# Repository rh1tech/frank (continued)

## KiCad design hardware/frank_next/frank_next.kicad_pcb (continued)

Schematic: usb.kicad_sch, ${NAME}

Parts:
C71: 100nF; C_0603_1608Metric
C72, C73: 100uF; CP_Elec_6.3x6.0
C74, C75, C79, C81, C83: 100nF; C_0603_1608Metric; LCSC C14663
C76, C77, C78, C80, C82, C84, C86, C87, C88: 10uF; C_0603_1608Metric; LCSC C96446
C85: 1uF; C_0603_1608Metric; LCSC C29936
C89, C90: 12pF; C_0603_1608Metric; LCSC C38523
C91: 22pF; C_0603_1608Metric; LCSC C1653
J10, J11: USB4215-03-A; USB_C_Receptacle; LCSC C37616412
JP4: USB Debug; SolderJumper-2_P1.3mm_Open_RoundedPad1.0x1.5mm
JP5: PWR Debug; SolderJumper-2_P1.3mm_Open_RoundedPad1.0x1.5mm
L5: 330R 2A; L_0805_2012Metric; LCSC C76819
L6: 2.2uH; L_Cenker_CKCS3015; LCSC C167747
LD3: Green; LED_0603_1608Metric; LCSC C965804
R49: 10K; R_0603_1608Metric
R50, R51, R52, R53: 5.1K; R_0603_1608Metric; LCSC C23186
R54: 300K; R_0603_1608Metric; LCSC C23024
R55, R58, R62: 100K; R_0603_1608Metric; LCSC C25803
R56: 1M; R_0603_1608Metric; LCSC C22935; not fitted
R57, R60: 1K; R_0603_1608Metric; LCSC C21190
R59: 10K; R_0603_1608Metric; LCSC C2906982
R61: 4.7K; R_0603_1608Metric; LCSC C23162; not fitted
R63: 22K; R_0603_1608Metric; LCSC C31850
S7: SS12D00; Switch_Slide_SS12D00; Mouser Part Number 611-SK12D07VG3NS
S8: SK12D07VG3NS; Switch_Slide_SK12D07VG3NS_PWR; Mouser Part Number 611-SK12D07VG3NS; LCSC C431547
U12: TS3USB221RSER; UQFN-10
U13, U14: TPD4S012DRYR; Mouser Part Number 595-TPD4S012DRYR; LCSC C96506
U15: TPS2116DRL; SOT-583-8; LCSC C3235557
U16: AO3401A; SOT-23-3L_AOS; LCSC C15127
U17: TS3USB221RSER; UQFN-10; LCSC C130085
U18: SY8089AAAC; SOT-23-5; LCSC C78988
U19: CH334F; QFN-24-1EP_4x4mm_P0.5mm_EP2.7x2.7mm; LCSC C5187527
Y4: 12 MHz; Crystal_SMD_3225-4Pin_3.2x2.5mm; LCSC C9002

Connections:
+3V3: C71.1, C81.2, C86.1, C87.1, C91.1, JP4.1 (A), L6.1, R49.1, R57.2, R62.1, S7.2, U12.10 (VCC), U17.10 (VCC); also elsewhere on the board
/CH343P/UD+: U12.1 (1D+); also elsewhere on the board
/CH343P/UD-: U12.2 (1D-); also elsewhere on the board
/RP2350A/D+: U12.3 (2D+); also elsewhere on the board
/RP2350A/D-: U12.4 (2D-); also elsewhere on the board
/RP2350B/D+: U17.8 (D+); also elsewhere on the board
/RP2350B/D-: U17.7 (D-); also elsewhere on the board
/USB/+5V_BUCK: C80.1, C82.1, C83.1, L5.2, U18.1 (EN), U18.4 (IN)
/USB/D2+: J10.6 (DP1), J10.8 (DP2), U13.1 (D+), U17.1 (1D+)
/USB/D2-: J10.5 (DN2), J10.7 (DN1), U13.2 (D-_), U17.2 (1D-)
/USB/DH+: U17.3 (2D+), U19.15 (DPU+)
/USB/DH-: U17.4 (2D-), U19.14 (DMU-)
/USB/DS1+: U19.12 (DP1+); also elsewhere on the board
/USB/DS1-: U19.11 (DM1-); also elsewhere on the board
/USB/DS2+: U19.10 (DP2+); also elsewhere on the board
/USB/DS2-: U19.9 (DM2-); also elsewhere on the board
/USB/DS3+: U19.8 (DP3+); also elsewhere on the board
/USB/DS3-: U19.7 (DM3-); also elsewhere on the board
/USB/OVCUR: U19.1 (~OVCUR); also elsewhere on the board
/USB/PWREN: U19.24 (~PWREN); also elsewhere on the board
/USB/S: JP4.2 (B), R59.2, S7.3, U17.9 (S)
/USB/ST: R56.2, U15.8 (ST)
/USB/USBC_D+: J11.6 (DP1), J11.8 (DP2), U12.8 (D+), U14.1 (D+)
/USB/USBC_D-: J11.5 (DN2), J11.7 (DN1), U12.7 (D-), U14.2 (D-_)
/USB/VBUS_IN: C78.1, C79.2, R58.2, U15.2 (VOUT), U15.7 (VOUT), U16.2 (S)
/USB/VBUS_IN1: C74.2, C76.2, J11.2 (VBUS), J11.11 (VBUS), R54.2, U14.6 (VBUS), U15.3 (VIN1), U15.5 (MODE)
/USB/VBUS_IN2: C75.2, C77.2, J10.2 (VBUS), J10.11 (VBUS), U13.6 (VBUS), U15.6 (VIN2)
/USB/VDD33: C84.2, C85.2, U19.20 (VDD33_{LDO})
/USB/XTAL_N: C89.1, U19.3 (XO), Y4.3
/USB/XTAL_P: C90.1, U19.4 (XI), Y4.1
/USB_SEL: R49.2, U12.9 (S); also elsewhere on the board
GND: C71.2, C72.2, C73.2, C74.1, C75.1, C76.1, C77.1, C78.2, C80.2, C81.1, C82.2, C83.2, C84.1, C85.1, C86.2, C87.2, C88.1, C89.2, C90.2, J10.1 (GND), J10.12 (GND), J10.13 (SHIELD), J11.1 (GND), J11.12 (GND), J11.13 (SHIELD), JP5.1 (A), LD3.1 (K), R50.1, R51.1, R52.1, R53.1, R55.1, R59.1, R61.2, R63.2, S8.2, U12.5 (GND), U12.6 (~OE), U13.4 (GND), U14.4 (GND), U15.1 (GND), U17.5 (GND), U17.6 (~OE), U18.2 (GND), U19.25 (GND), Y4.2, Y4.4; also elsewhere on the board
unnamed: J10.4 (CC1), R50.2
unnamed: J10.10 (CC2), R51.2
unnamed: J11.4 (CC1), R52.2
unnamed: J11.10 (CC2), R53.2
unnamed: JP5.2 (B), R60.2, S8.3
unnamed: LD3.2 (A), R57.1
unnamed: R54.1, R55.2, R56.1, U15.4 (PR1)
unnamed: C79.1, R58.1, R60.1, U16.1 (G)
unnamed: C91.2, R62.2, R63.1, U18.5 (FB)
unnamed: L6.2, U18.3 (LX)
unnamed: R61.1, U19.18 (PSELF)
VBUS: C72.1, C73.1, C88.2, L5.1, U16.3 (D), U19.19 (V5); also elsewhere on the board

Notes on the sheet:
USB-A shared VBUS bulk: C102 + C103 = 200 uF USB 2.0 7.2.4.1: >= 120 uF per hub, may be shared Kyocera AVX APZ0606101M016R 100 uF 16 V aluminium polymer, ESR 30 mOhm

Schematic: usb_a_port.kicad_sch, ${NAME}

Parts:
C95: 100nF; C_0603_1608Metric; LCSC C14663
C96: 10uF; C_0603_1608Metric; LCSC C96446
J12: 676430910; USB_A_Short; LCSC C2798029
R65: 100K; R_0603_1608Metric; LCSC C25803
U21: TPD4S012DRYR; Mouser Part Number 595-TPD4S012DRYR; LCSC C96506
U22: CH217K; SOT-23-6; LCSC C7462749

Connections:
/USB/DS1+: J12.3 (D+), U21.1 (D+); also elsewhere on the board
/USB/DS1-: J12.2 (D-), U21.2 (D-_); also elsewhere on the board
/USB/OVCUR: U22.3 (FLAG#); also elsewhere on the board
/USB/PWREN: U22.4 (EN#); also elsewhere on the board
/USB/USB A Port 1/VBUS_P: C95.1, J12.1 (VBUS), U21.6 (VBUS), U22.1 (VOUT)
GND: C95.2, C96.1, J12.4 (GND), J12.5 (Shield), R65.1, U21.4 (GND), U22.2 (GND); also elsewhere on the board
unnamed: R65.2, U22.5 (ISET)
VBUS: C96.2, U22.6 (VIN); also elsewhere on the board

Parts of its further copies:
C97, C99: 100nF; C_0603_1608Metric; LCSC C14663
C98, C101: 10uF; C_0603_1608Metric; LCSC C96446
J13, J14: 676430910; USB_A_Short; LCSC C2798029
R66, R70: 100K; R_0603_1608Metric; LCSC C25803
U23, U25: TPD4S012DRYR; Mouser Part Number 595-TPD4S012DRYR; LCSC C96506
U24, U27: CH217K; SOT-23-6; LCSC C7462749

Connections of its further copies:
/USB/DS2+: J13.3 (D+), U23.1 (D+); also elsewhere on the board
/USB/DS2-: J13.2 (D-), U23.2 (D-_); also elsewhere on the board
/USB/DS3+: J14.3 (D+), U25.1 (D+); also elsewhere on the board
/USB/DS3-: J14.2 (D-), U25.2 (D-_); also elsewhere on the board
/USB/OVCUR: U24.3 (FLAG#), U27.3 (FLAG#); also elsewhere on the board
/USB/PWREN: U24.4 (EN#), U27.4 (EN#); also elsewhere on the board
/USB/USB A Port 2/VBUS_P: C97.1, J13.1 (VBUS), U23.6 (VBUS), U24.1 (VOUT)
/USB/USB A Port 3/VBUS_P: C99.1, J14.1 (VBUS), U25.6 (VBUS), U27.1 (VOUT)
GND: C97.2, C98.1, C99.2, C101.1, J13.4 (GND), J13.5 (Shield), J14.4 (GND), J14.5 (Shield), R66.1, R70.1, U23.4 (GND), U24.2 (GND), U25.4 (GND), U27.2 (GND); also elsewhere on the board
unnamed: R66.2, U24.5 (ISET)
unnamed: R70.2, U27.5 (ISET)
VBUS: C98.2, C101.2, U24.6 (VIN), U27.6 (VIN); also elsewhere on the board

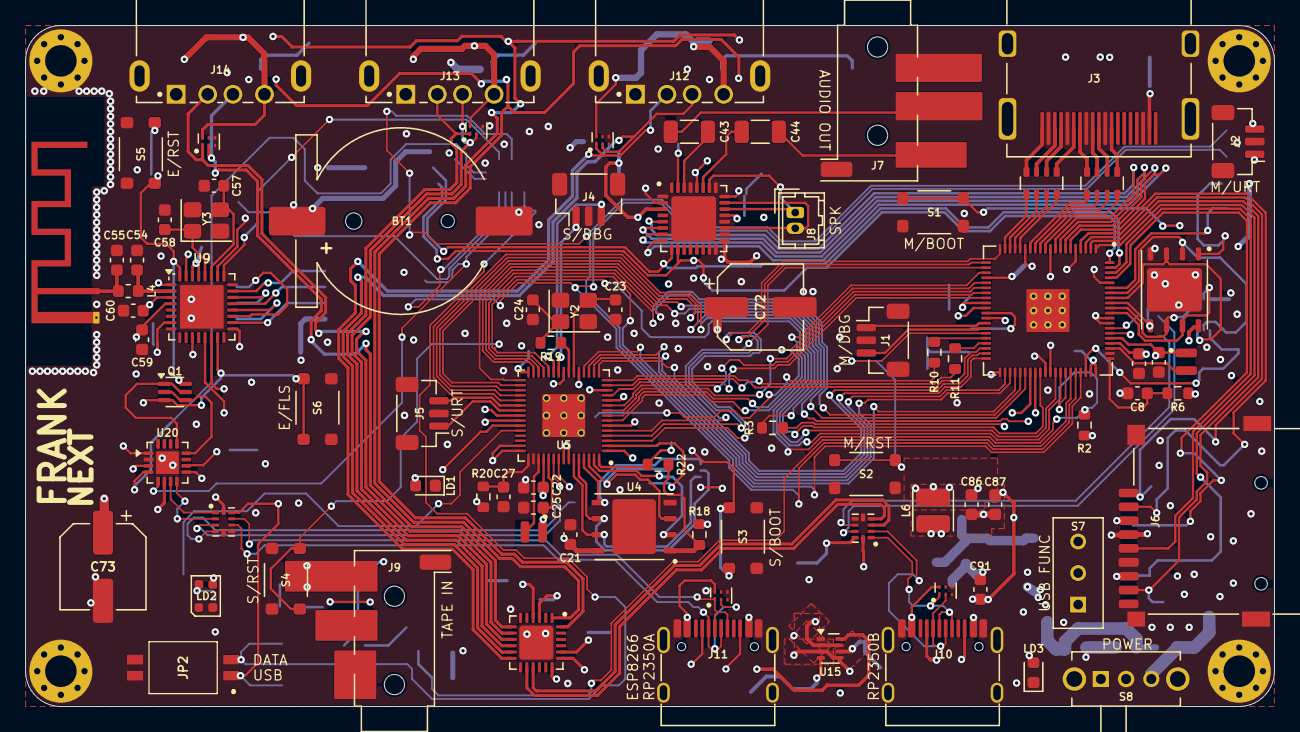
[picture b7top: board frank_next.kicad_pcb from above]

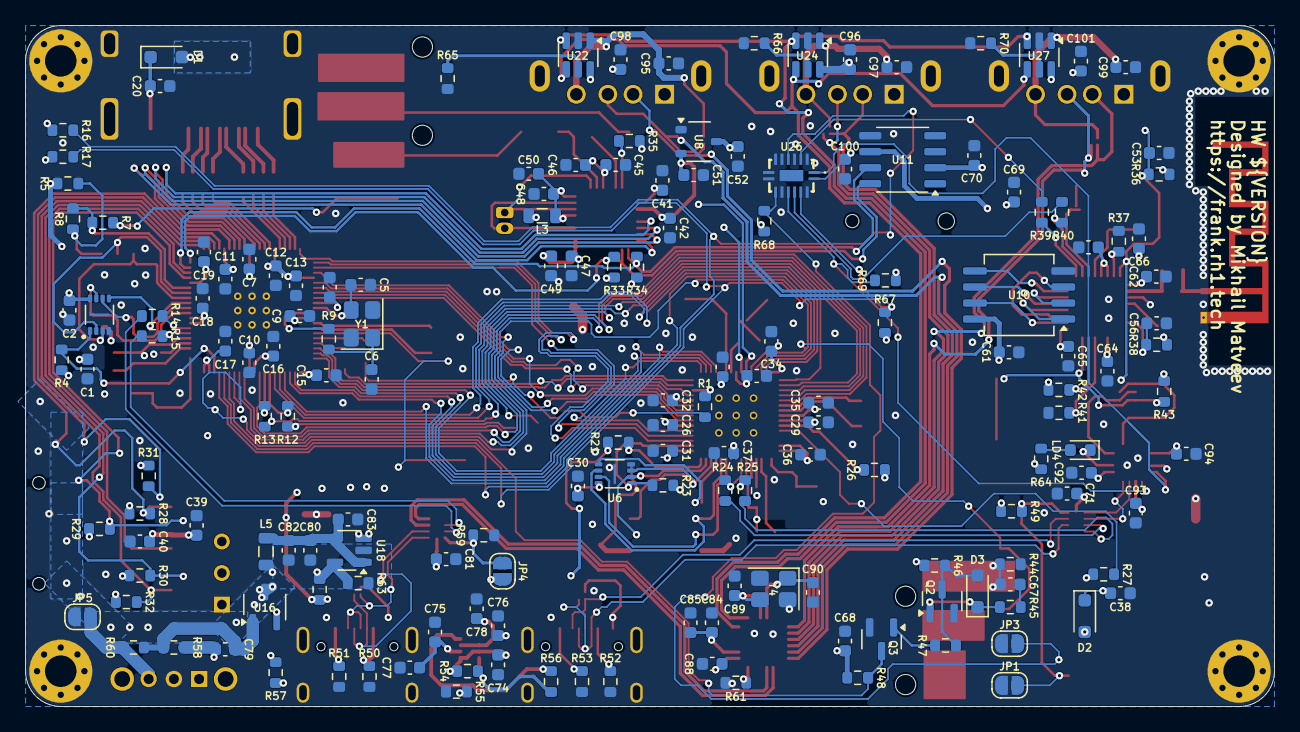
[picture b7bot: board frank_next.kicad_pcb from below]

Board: 4 copper layers, 99.0 x 54.0 mm, 253 parts (165 on the bottom side), 203 nets.

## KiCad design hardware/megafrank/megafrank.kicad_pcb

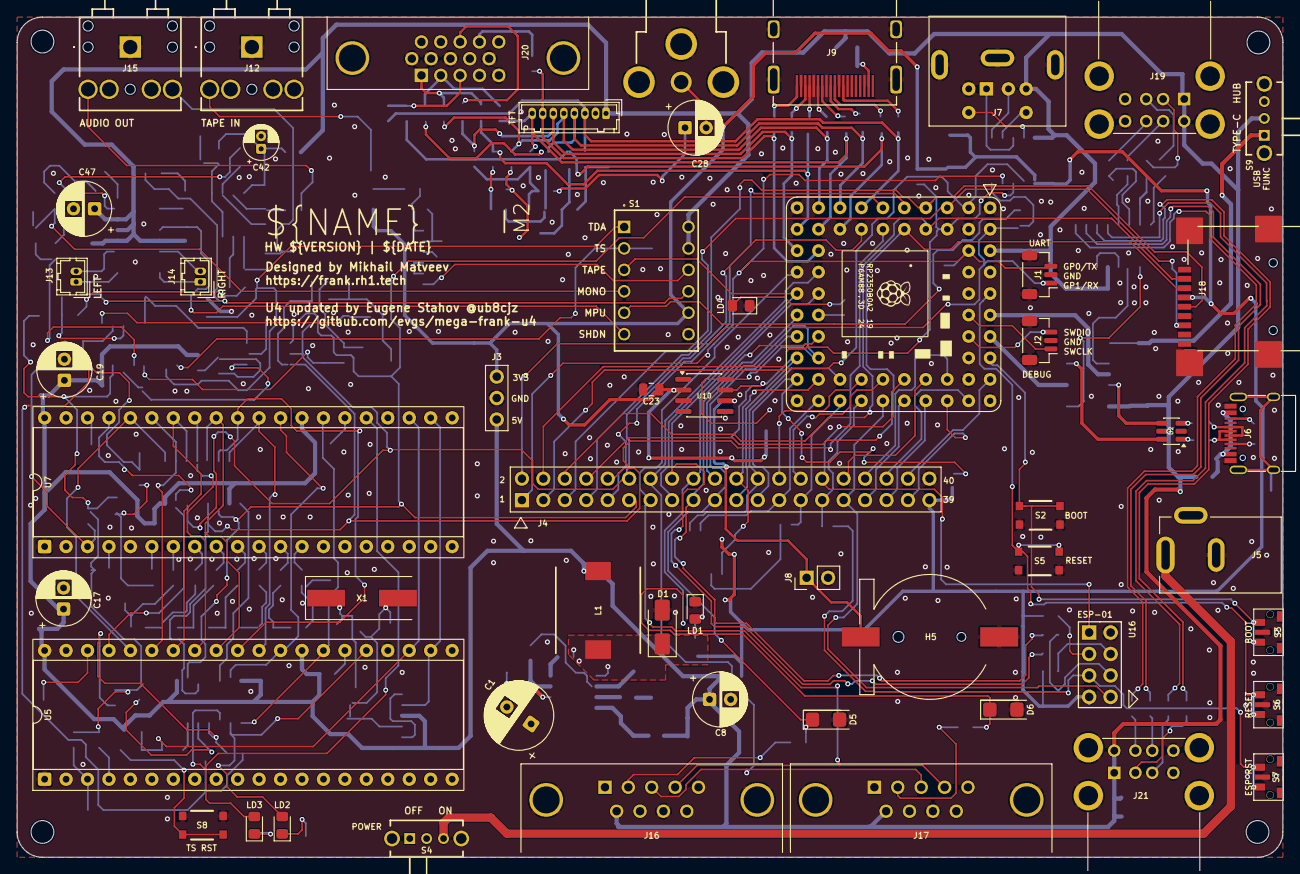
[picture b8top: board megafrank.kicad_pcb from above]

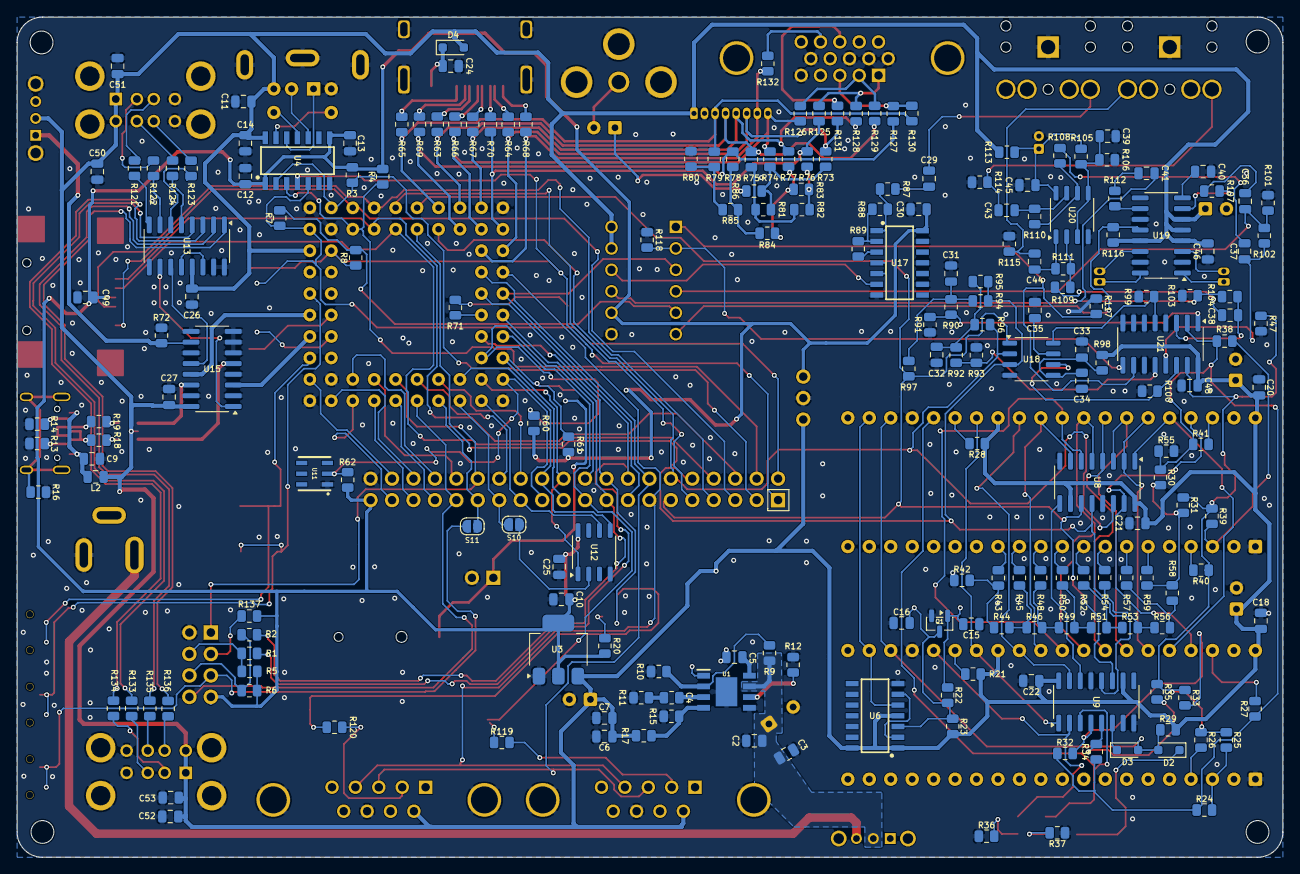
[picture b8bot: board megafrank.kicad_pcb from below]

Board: 2 copper layers, 149.9 x 99.5 mm, 262 parts (204 on the bottom side), 223 nets.

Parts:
C1: 680u; C_Radial_D8.0mm_P3.50mm
C2, C7, C10, C33, C35, C37, C38, C39, C43, C44, C50, C51, C52, C53: 10u; C_0805_2012Metric
C3, C5, C6, C9, C11, C12, C13, C14, C18, C20, C21, C22, C23, C24, C25, C27, C29, C30, C34, C40, C45, C48, C49: 100n; C_0805_2012Metric
C4: 150pF; R_0805_2012Metric
C8, C28: 220u; C_Radial_D6.3mm_P2.50mm
C15, C16: 22p; C_0805_2012Metric
C17, C19, C47: 100u; C_Radial_D6.3mm_P2.50mm
C26: 4.7u; C_0805_2012Metric
C31, C32: 47n; C_0805_2012Metric
C36, C41, C46: 1u; C_0805_2012Metric
C42: 10u; CP_Radial_D4.0mm_P1.50mm
D1: 1N5822; D_SMA
D2, D3: 1N4148; D_SOD-323
D4: 1N5819WS; D_SOD-323
D5, D6: 3V3; D_MiniMELF
H1, H2, H3, H4: Hole 2.7mm; MountingHole_2.7mm
H5: Battery_CR1220
J1: UART; JST_SH_1x03_P1.00mm_Vertical
J2: DEBUG; JST_SH_1x03_P1.00mm_Vertical
J3: PWR; PinHeader_1x03_P2.54mm
J4: Conn_02x20_Odd_Even; PinHeader_2x20_P2.54mm_Vertical
J5: DC-005-5A-2.0; BarrelJack_DC-005
J6: USB4215-03-A; USB_C_Receptacle
J7: MDC-036; MiniDIN_6pin_Female
J8: BAT 3V; PinHeader_1x02_P2.54mm_Vertical
J9: DC3RX19JA2; HDMI_Female
J10: RCA-103; BarrelJack_RCJ-012
J11: Pin Header 1x08; JST_GH_1x08_P1.25mm
J12, J15: SJ1-3525N; AudioJack_3.5mm_SJ1-3525N
J13: PAM L; JST_GH_1x02_P1.25mm
J14: PAM R; JST_GH_1x02_P1.25mm
J16, J17: GP2; DSUB-9_Male_TopMount
J18: 104031-0811; MicroSD_SMD_Long
J19, J21: SS-52100-004; USB_A_Stacked
J20: VGA; DSUB-15_Female
L1: 22uH; Inductor_CDRH104RNP
L2: 330R; C_0805_2012Metric
LD1: Green; LED_0805
LD2, LD3: Orange; LED_0805
LD4: Blue; LED_0805
Q1: BC850; SOT-23
R1, R2, R20, R21, R23, R28, R36, R37, R71, R96, R97, R119, R120, R128, R129, R130: 1K; R_0805_2012Metric
R3, R4, R5, R6, R7, R8, R29, R30, R31, R32, R33, R34, R35, R44, R46, R49, R51, R53, R56, R58, R72, R90, R92, R101, R102, R103, R104, R105, R106, R107, R108, R109, R112, R116, R117, R118, R137: 10K; R_0805_2012Metric
R9, R11, R12, R22, R88, R89: 100K; R_0805_2012Metric
R10: 24K; R_0805_2012Metric
R13, R14: 5.1K; R_0805_2012Metric
R15: 8.2K; R_0805_2012Metric
R16: 1M; R_0805_2012Metric
R17: 43K; R_0805_2012Metric
R18, R19, R121, R122, R123, R124, R133, R134, R135, R136: 22R; R_0805_2012Metric
R24, R25, R38, R39, R60, R61, R62, R87: 4.7K; R_0805_2012Metric
R26, R27, R40, R41, R91, R93, R94, R95: 2K; R_0805_2012Metric
R42, R43, R45, R48, R50, R52, R54, R57, R59, R114, R115: 20K; R_0805_2012Metric
R47, R55: 120R; R_0805_2012Metric
R63, R64, R65, R66, R67, R68, R69, R70, R74, R75, R76, R77, R78, R79: 270R; R_0805_2012Metric
R73: 750R; R_0805_2012Metric
R80: 300R; R_0805_2012Metric
R81, R82, R83, R84, R85: 150R; R_0805_2012Metric
R86: 51R; R_0805_2012Metric
R98, R113, R131, R132: 100R; R_0805_2012Metric
R99, R100: 470R; R_0805_2012Metric
R110, R111: 47K; R_0805_2012Metric
R125, R126, R127: 330R; R_0805_2012Metric
S1: DS01-254-S-06BE
S2: RP BOOT; Button_SMD_3x4x2mm
S3: RP BOOT; Button_SMD_TS1234VW
S4, S9: SK12D07VG3NS; Switch_Slide_SK12D07VG3NS
S5: RP Reset; Button_SMD_3x4x2mm
S6: RP Reset; Button_SMD_TS1234VW
S7: ESP Reset; Button_SMD_TS1234VW
S8: TS Reset; Button_SMD_3x4x2mm
S10: PSRAM On; SolderJumper-2_P1.3mm_Open_RoundedPad1.0x1.5mm
S11: PICO-ESP-RESET; SolderJumper-2_P1.3mm_Open_RoundedPad1.0x1.5mm
U1: MP1584EN-LF-Z; SOIC-9_P1.27mm
U2: USBLC6-2SC6; SOT-23-6
U3: AMS1117 3.3; SOT-223-3_TabPin2
U4: TXS0104EDR; SOIC-14_P1.27mm
U5, U7: JFC95101; DIP-40_W15.24mm_Socket
U6: 74HC74; SOIC-14_P1.27mm
U8, U9: 74HC595; SOP-16_P1.27mm
U10: DS3231MZ; SOIC-8_3.9x4.9mm_P1.27mm
U11: DS2401P+; TSOC-6
U12: ESP-PSRAM64; SO-8
U13: MW7211A; SOP-16_P1.27mm
U14: Pimoroni PGA2350; PGA2350
U15, U21: 74HC4052D; SOP-16_P1.27mm
U16: ESP-01v090; ESP-01S
U17: CD4069UBM; SOIC-14_P1.27mm
U18: TDA1387T; SO-8
U19: PAM8403D; SOP-16_P1.27mm
U20: LM358; SO-8
X1: 3.58 MHz; Crystal_HC49-S

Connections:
+3V3: C10.1, C12.1, C13.1, C23.1, C25.1, C30.1, C49.2, J3.1, J4.39, J18.4 (VDD), R3.2, R4.2, R5.2, R6.2, R20.2, R60.2, R61.2, R62.1, R137.2, S1.11, U3.2 (VO), U4.1 (VCCA), U4.8 (OE), U10.2 (VCC), U12.8 (VCC), U16.7 (VCC), U17.14 (VDD)
/Audio Multiplexer/AMP_IN_L: C37.1, R102.1, U21.13 (1Z)
/Audio Multiplexer/AMP_IN_R: C38.1, R104.1, U21.3 (2Z)
/Audio Multiplexer/PWM_OUT_L: R92.2, R93.1, U21.12 (1Y0)
/Audio Multiplexer/PWM_OUT_R: R90.2, R91.1, U21.1 (2Y0)
/Audio Multiplexer/SW_TDA: R117.2, S1.1, U21.10 (S0)
/Audio Multiplexer/SW_TS: R118.2, S1.2, U21.9 (S1)
/Audio Multiplexer/TDA_L: R100.2, U18.6 (A_LEFT), U21.14 (1Y1)
/Audio Multiplexer/TDA_R: R99.1, U18.8 (A_RIGHT), U21.5 (2Y1)
/Audio/AMP_OUTL: C43.2, J15.2 (TIP), R114.2
/Audio/AMP_OUTR: C44.2, J15.3 (RING), R115.2
/Audio/AMP_PAM_OUTL_M: J13.2, U19.3 (-OUTL)
/Audio/AMP_PAM_OUTL_P: J13.1, U19.1 (+OUT_L)
/Audio/AMP_PAM_OUTR_M: J14.2, U19.14 (-OUT_R)
/Audio/AMP_PAM_OUTR_P: J14.1, U19.16 (+OUT_R)
/Audio/TS/A1: R26.2, U5.4 (B)
/Audio/TS/A2: R40.2, U7.4 (B)
/Audio/TS/B1: R24.2, R25.2, U5.3 (A)
/Audio/TS/B2: R38.2, R39.2, U7.3 (A)
/Audio/TS/BEEP: R32.2, R33.2, U9.4 (QE)
/Audio/TS/C1: R27.2, U5.38 (C)
/Audio/TS/C2: R41.2, U7.38 (C)
/Audio/TS/CLK_1.75M: U5.22 (CLOCK), U6.5 (Q), U7.22 (CLOCK)
/Audio/TS/COVOX_OUT: R30.2, R31.2, R58.2, R59.1
/Audio/TS/DA0: U5.37 (DA0), U7.37 (DA0), U8.15 (QA)
/Audio/TS/DA1: U5.36 (DA1), U7.36 (DA1), U8.1 (QB)
/Audio/TS/DA2: U5.35 (DA2), U7.35 (DA2), U8.2 (QC)
/Audio/TS/DA3: U5.34 (DA3), U7.34 (DA3), U8.3 (QD)
/Audio/TS/DA4: U5.33 (DA4), U7.33 (DA4), U8.4 (QE)
/Audio/TS/DA5: U5.32 (DA5), U7.32 (DA5), U8.5 (QF)
/Audio/TS/DA6: U5.31 (DA6), U7.31 (DA6), U8.6 (QG)
/Audio/TS/DA7: U5.30 (DA7), U7.30 (DA7), U8.7 (QH)
/Audio/TS/DAC0: R43.2, U7.13 (IOB0)
/Audio/TS/DAC1: R45.2, U7.12 (IOB1)
/Audio/TS/DAC2: R48.2, U7.11 (IOB2)
/Audio/TS/DAC3: R50.2, U7.10 (IOB3)
/Audio/TS/DAC4: R52.2, U7.9 (IOB4)
/Audio/TS/DAC5: R54.2, U7.8 (IOB5)
/Audio/TS/DAC6: R57.2, U7.7 (IOB6)
/Audio/TS/DAC7: R59.2, U7.6 (IOB7)
/Audio/TS/L_IN: R25.1, R26.1, R31.1, R33.1, R35.1, R39.1, R40.1, R47.1, U21.15 (1Y2)
/Audio/TS/R_IN: R24.1, R27.1, R30.1, R32.1, R34.1, R38.1, R41.1, R55.1, U21.2 (2Y2)
/Audio/TS/SAVE: R34.2, R35.2, U9.5 (QF)
/Audio/TS/YM_BC1: U5.29 (BC1), U7.29 (BC1), U9.15 (QA)
/Audio/TS/YM_BDIR: U5.27 (BDIR), U7.27 (BDIR), U9.1 (QB)
/Audio/TS/YM_CS1: LD2.2 (A), U5.25 (A8), U9.2 (QC)
/Audio/TS/YM_CS2: LD3.2 (A), U7.25 (A8), U9.3 (QD)
/Audio/TS/YM_RST: D2.2 (A), D3.2 (A), R29.1, U5.23 (~RESET), U7.23 (~RESET)
/Audio/TS/YM_SEL1: R21.2, U5.26 (~SEL)
/Audio/TS/YM_SEL2: R28.2, U7.26 (~SEL)
/Composite/CVBS: C28.2, J10.1
/ESP01S/CH_PD: R137.1, U16.3 (CH_PD)
/ESP01S/GPIO0: R2.1, R6.1, U16.6 (GPIO0)
/ESP01S/GPIO2: R1.1, R5.1, U16.4 (GPIO2)
/ESPRST: S7.1, S11.1 (A), U16.5 (RST)
/MONO_L: C36.1, R101.1, R102.2, S1.4
/MONO_R: C41.1, R103.1, R104.2, S1.10
/MSPUP3V3: R7.2, R8.2, S1.5
/PBOOTSEL: S2.1, S2.3, S3.1, U14.51 (BOOTSEL)
/PGPIO0: J1.1, J4.1, R8.1, U4.4 (A3), U14.61 (GP0)
/PGPIO1: J1.3, J4.2, R7.1, U4.5 (A4), U14.62 (GP1)
/PGPIO2: J4.3, R3.1, U4.2 (A1), U14.2 (GP2)
/PGPIO3: J4.4, R4.1, U4.3 (A2), U14.3 (GP3)
/PGPIO4: J4.5, J18.7 (DAT0), U14.4 (GP4)
/PGPIO5: J4.6, J18.2 (DAT3/CD), U14.5 (GP5)
/PGPIO6: J4.7, J18.5 (CLK), U14.6 (GP6)
/PGPIO7: J4.8, J18.3 (CMD), U14.7 (GP7)
/PGPIO8: J4.9, U14.8 (GP8)
/PGPIO9: J4.10, R94.1, R95.1, U8.12 (RCLK), U9.12 (RCLK), U14.9 (GP9), U18.3 (DATA)
/PGPIO10: J4.11, R97.2, U8.11 (SRCLK), U9.11 (SRCLK), U14.10 (GP10), U18.1 (SCLK)
/PGPIO11: J4.12, R96.2, U8.14 (SER), U14.11 (GP11), U18.2 (LRCK)
/PGPIO12: J11.3, R65.2, R79.1, R130.1, U14.12 (GP12)
/PGPIO13: R69.2, R78.1, R127.1, U14.13 (GP13)
/PGPIO14: J11.4, R63.2, R75.1, R129.1, U14.14 (GP14)
/PGPIO15: J11.8, R66.2, R74.1, R126.1, U14.15 (GP15)
/PGPIO16: J11.5, R67.2, R77.1, R128.1, U14.16 (GP16)
/PGPIO17: R70.2, R76.1, R125.1, U14.17 (GP17)
/PGPIO18: J11.6, R64.2, R73.1, R131.2, U14.19 (GP18)
/PGPIO19: J11.7, R68.2, R132.2, U14.20 (GP19)
/PGPIO20: J4.13, J16.4, J17.4, U14.21 (GP20)
/PGPIO21: J4.14, J16.3, J17.3, U14.22 (GP21)
/PGPIO22: J4.15, S1.3, U14.23 (GP22)
/PGPIO23: J4.16, R1.2, U14.24 (GP23)
/PGPIO24: J4.17, R2.2, U14.25 (GP24)
/PGPIO26: D5.1 (K), J4.19, R119.1, U14.27 (GP26)
/PGPIO27: D6.1 (K), J4.18, R120.1, U14.28 (GP27)
/PGPIO28: J4.21, R61.1, U10.7 (SDA), U14.29 (GP28)
/PGPIO29: J4.20, R60.1, U10.8 (SCL), U14.30 (GP29)
/PGPIO30: J4.23, R62.2, U11.2 (DATA), U14.31 (GP30)
/PGPIO31: J4.22, U12.1 (~CE), U14.32 (GP31)
/PGPIO32: J4.25, U12.6 (SCLK), U14.34 (GP32)
/PGPIO33: J4.24, U12.5 (SI/SIO), U14.35 (GP33)
/PGPIO34: J4.27, S10.2 (B), U14.36 (GP34)
/PGPIO35: J4.26, U14.37 (GP35)
/PGPIO36: J4.29, S11.2 (B), U14.38 (GP36)
/PGPIO37: J4.28, U14.39 (GP37)
/PGPIO38: J4.31, U14.40 (GP38), U16.8 (URXD)
/PGPIO39: J4.30, U14.41 (GP39), U16.1 (UTXD)
/PGPIO40: J4.33, U14.42 (GP40)
/PGPIO41: J4.32, U14.43 (GP41)
/PGPIO42: J4.35, U14.44 (GP42)
/PGPIO43: J4.34, U14.45 (GP43)
/PGPIO44: J4.37, U14.46 (GP44)
/PGPIO45: J4.36, U14.47 (GP45)
/PGPIO46: J4.38, U14.49 (GP46)
/PRUN: S5.1, S5.3, S6.1, U14.56 (RUN)
/PS2/KB_CLK_5V: J7.5, U4.13 (B1)
/PS2/KB_DATA_5V: J7.1, U4.12 (B2)
/PS2/MS_CLK_5V: J7.6, U4.11 (B3)
/PS2/MS_DATA_5V: J7.2, U4.10 (B4)
/PSWCLK: J2.3, U14.55 (SWCLK)
/PSWDIO: J2.1, U14.52 (SWDIO)
/Power/D+: J6.6 (DP1), J6.8 (DP2), R19.2
/Power/D-: J6.5 (DN2), J6.7 (DN1), R18.2
/Power/DM: U2.6 (I/O1), U15.5 (2Y1)
/Power/DP: U2.4 (I/O2), U15.14 (1Y1)
/Power/VBUS_IN: C1.1, C2.1, C3.1, R9.2, S4.2, U1.7 (VIN)
/SHND: R116.2, S1.6, U19.12 (SHND)
/TC_DM: U14.53 (USB_DM), U15.3 (2Z)
/TC_DP: U14.54 (USB_DP), U15.13 (1Z)
/Tape In/LOAD_IN: S1.9, U17.6 (I=*C)
/Tape In/TAPE: C29.2, J12.2 (TIP)
/UM_SW: R72.2, S9.1, U15.10 (S0)
/USB Hub/DM1: R122.1, U13.7 (DM3)
/USB Hub/DM2: R124.1, U13.5 (DM2)
/USB Hub/DM3: R134.1, U13.3 (DM1)
/USB Hub/DM4: R136.1, U13.1 (DM0)
/USB Hub/DM_IN: U13.10 (DMU), U15.1 (2Y0)
/USB Hub/DP1: R121.1, U13.8 (DP3)
/USB Hub/DP2: R123.1, U13.6 (DP2)
/USB Hub/DP3: R133.1, U13.4 (DP1)
/USB Hub/DP4: R135.1, U13.2 (DP0)
/USB Hub/DP_IN: U13.11 (DPU), U15.12 (1Y0)
GND: C1.2, C2.2, C3.2, C6.1, C7.2, C8.2, C9.2, C10.2, C11.2, C12.2, C13.2, C14.2, C15.1, C16.1, C17.2, C18.2, C19.2, C20.2, C21.2, C22.2, C23.2, C24.2, C25.2, C26.2, C27.1, C30.2, C31.2, C32.2, C33.2, C34.2, C35.2, C39.1, C40.2, C42.2, C45.1, C46.2, C47.2, C48.1, C49.1, C50.2, C51.2, C52.2, C53.2, D1.2 (A), D5.2 (A), D6.2 (A), H5.2 (-), J1.2, J2.2, J3.2, J4.40, J5.2, J6.1 (GND), J6.12 (GND), J7.3, J8.2, J9.2 (G_D2), J9.5 (G_D1), J9.8 (G_D0), J9.11 (G_CLK), J9.17 (G_DDC/CEC), J9.20 (SHIELD1), J9.21 (SHIELD2), J9.22 (SHIELD3), J9.23 (SHIELD4), J10.2, J11.2, J12.1 (SLEEVE), J15.1 (SLEEVE), J16.8, J17.8, J18.6 (VSS), J18.SH (SHIELD), J19.4 (GND1), J19.8 (GND2), J19.SH (Shield), J20.0, J20.5, J20.6, J20.7, J20.8, J20.10, J21.4 (GND1), J21.8 (GND2), J21.SH (Shield), LD1.1 (K), LD4.1 (K), Q1.2 (E), R10.2, R11.2, R12.2, R13.1, R14.1, R15.1, R16.1, R36.1, R37.1, R42.1, R47.2, R55.2, R72.1, R80.1, R91.2, R93.2, R99.2, R100.1, R101.2, R103.2, R106.1, R114.1, R115.1, R117.1, R118.1, S1.12, S2.2, S2.4, S3.2, S3.3 (GND), S5.2, S5.4, S6.2, S6.3 (GND), S7.2, S7.3 (GND), S8.2, S8.4, S9.4 (MH1), S9.5 (MH2), U1.5 (GND), U1.9 (EP), U2.2 (GND), U3.1 (GND), U4.7 (GND), U5.1 (VSS), U5.24 (~A9), U6.7 (GND), U7.1 (VSS), U7.24 (~A9), U8.8 (GND), U8.13 (~OE), U9.8 (GND), U9.13 (~OE), U10.5 (GND), U11.1 (GND), U12.4 (VSS), U13.15 (GND), U13.16 (GND), U14.1 (GND), U14.18 (GND), U14.33 (GND), U14.48 (GND), U15.2 (2Y2), U15.4 (2Y3), U15.6 (~E), U15.7 (VEE), U15.8 (GND), U15.9 (S1), U15.11 (1Y3), U15.15 (1Y2), U16.2 (GND), U17.7 (VSS), U17.9 (D14), U17.11 (E), U17.13 (F), U18.4 (AGND), U19.2 (PGND), U19.11 (GND), U19.15 (PGND), U20.4 (V-), U21.4 (2Y3), U21.6 (~E), U21.7 (VEE), U21.8 (GND), U21.11 (1Y3)
GP25: R71.2, U14.26 (GP25)
unnamed: C4.2, R11.1
unnamed: C9.1, J6.2 (VBUS), J6.11 (VBUS), L2.2
unnamed: C28.1, R86.2
unnamed: C29.1, R87.2
unnamed: C31.1, R90.1, R94.2, R97.1
unnamed: C32.1, R92.1, R95.2, R96.1
unnamed: C36.2, R107.2
unnamed: C37.2, R108.2
unnamed: C38.2, R109.2
unnamed: C41.2, R112.2
unnamed: C43.1, R110.1, U20.7
unnamed: C44.1, R111.1, U20.1
unnamed: C5.2, D1.1 (K), L1.1, U1.1 (SW)
unnamed: D2.1 (K), S8.1, S8.3
unnamed: D3.1 (K), U9.6 (QG)
unnamed: C24.1, D4.1 (K), J9.18 (+5V)
unnamed: H5.1 (+), J8.1, U10.6 (VBAT)
unnamed: J5.1, S4.3
unnamed: J6.4 (CC1), R13.2
unnamed: J6.10 (CC2), R14.2
unnamed: J6.13 (SHIELD), R16.2
unnamed: J9.12 (CLKN), R65.1
unnamed: J9.10 (CLKP), R69.1
unnamed: J9.9 (D0N), R63.1
unnamed: J9.7 (D0P), R66.1
unnamed: J9.6 (D1N), R67.1
unnamed: J9.4 (D1P), R70.1
unnamed: J9.3 (D2N), R64.1
unnamed: J9.1 (D2P), R68.1
unnamed: J16.2, R119.2
unnamed: J17.2, R120.2
unnamed: J19.3 (D1+), R121.2
unnamed: J19.2 (D1-), R122.2
unnamed: J19.7 (D2+), R123.2
unnamed: J19.6 (D2-), R124.2
unnamed: J20.1, R125.2, R128.2
unnamed: J20.2, R126.2, R129.2
unnamed: J20.3, R127.2, R130.2
unnamed: J20.13, R131.1
unnamed: J20.14, R132.1
unnamed: J21.3 (D1+), R133.2
unnamed: J21.2 (D1-), R134.2
unnamed: J21.7 (D2+), R135.2
unnamed: J21.6 (D2-), R136.2
unnamed: LD1.2 (A), R20.1
unnamed: LD2.1 (K), R36.2
unnamed: LD3.1 (K), R37.2
unnamed: LD4.2 (A), R71.1
unnamed: C15.2, Q1.1 (B), R22.1, X1.1
unnamed: C16.2, Q1.3 (C), R22.2, R23.1, U6.3 (C), X1.2
unnamed: R18.1, U2.1 (I/O1)
unnamed: R19.1, U2.3 (I/O2)
unnamed: R42.2, R43.1, R44.1
unnamed: R44.2, R45.1, R46.1
unnamed: R46.2, R48.1, R49.1
unnamed: R49.2, R50.1, R51.1
unnamed: R51.2, R52.1, R53.1
unnamed: R53.2, R54.1, R56.1
unnamed: R56.2, R57.1, R58.1
unnamed: R73.2, R74.2, R81.2, R86.1
unnamed: R75.2, R81.1, R82.2
unnamed: R76.2, R82.1, R83.2
unnamed: R77.2, R83.1, R84.2
unnamed: R78.2, R84.1, R85.2
unnamed: R79.2, R80.2, R85.1
unnamed: S10.1 (A), U12.2 (SO/SIO)
unnamed: C5.1, U1.8 (BST)
unnamed: C4.1, U1.3 (COMP)
unnamed: R9.1, R10.1, U1.2 (EN)
unnamed: R15.2, R17.2, U1.4 (FB)
unnamed: R12.1, U1.6 (FREQ)
unnamed: U6.2 (D), U6.6 (~Q)
unnamed: U8.9 (QH'), U9.14 (SER)
unnamed: U13.12 (VD33), U13.14 (VD3)
unnamed: R87.1, R88.2, U17.1 (A)
unnamed: R89.1, U17.3 (B)
unnamed: U17.4 (H=*B), U17.5 (C)
unnamed: R88.1, R89.2, U17.2 (G-*A)
unnamed: C35.1, U18.7 (FLT)
unnamed: C33.1, C34.1, R98.1, U18.5 (VA)
unnamed: R107.1, U19.7 (INL)
unnamed: R112.1, U19.10 (INR)
unnamed: C40.1, U19.8 (VREF)
unnamed: C39.2, R105.1, R106.2, U20.3 (+), U20.5 (+)
unnamed: R109.1, R111.2, U20.2 (-)
unnamed: R108.1, R110.2, U20.6 (-)
unnamed: C42.1, C45.2, R105.2, R113.2, U20.8 (V+)
VBUS: C6.2, C7.1, C8.1, C11.1, C14.1, C17.1, C18.1, C19.1, C20.1, C21.1, C22.1, C26.1, C27.2, C46.1, C47.1, C48.2, C50.1, C51.1, C52.1, C53.1, D4.2 (A), J3.3, J7.4, J11.1, J16.6, J17.6, J19.1 (VBUS1), J19.5 (VBUS2), J21.1 (VBUS1), J21.5 (VBUS2), L1.2, L2.1, R17.1, R21.1, R23.2, R28.1, R29.2, R98.2, R113.1, R116.1, S1.7, S1.8, S9.2, U2.5 (VBUS), U3.3 (VI), U4.14 (VCCB), U5.28 (BC2), U5.40 (VCC), U6.1 (~R), U6.4 (~S), U6.14 (VCC), U7.28 (BC2), U7.40 (VCC), U8.10 (~SRCLR), U8.16 (VCC), U9.10 (~SRCLR), U9.16 (VCC), U13.13 (VDD5), U14.60 (VBUS), U15.16 (VCC), U19.4 (PVDD), U19.5 (MUTE), U19.6 (VDD), U19.13 (PVDD), U21.16 (VCC)

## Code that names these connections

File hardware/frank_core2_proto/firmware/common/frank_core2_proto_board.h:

/*
 * FRANK Core 2 — dual-RP2350 test firmware
 *
 * Copyright (c) 2026 Mikhail Matveev <xtreme@rh1.tech>
 * https://github.com/rh1tech/frank
 * SPDX-License-Identifier: GPL-3.0-or-later
 */

/*
 * frank_core2_proto_board.h — GPIO map for the FRANK Core 2 board.
 *
 * Every assignment below was extracted from the KiCad netlist
 * (frank_core2.kicad_sch -> kicad-cli sch export netlist), so this file
 * is the single source of truth shared by the master and slave builds.
 *
 * U3 = RP2350B (master, QFN-80)   U6 = RP2350  (slave, QFN-60)
 *
 * The master carries all the user-facing peripherals: HDMI (J5), microSD
 * (J7), TDA1387 I2S DAC (U8), USB-C host/device (J8), WS2812B status LED
 * (LD1) and 8 MB PSRAM (U2) + 16 MB flash (U1).
 *
 * The slave carries its own 8 MB PSRAM (U5) + 16 MB flash (U4), a USB-C
 * port (J9), a blue status LED (LD2) and a UART header (J4). Everything
 * else it needs it gets over the inter-processor link.
 */
#ifndef FRANK_CORE2_BOARD_H
#define FRANK_CORE2_BOARD_H

/* =====================================================================
 * Inter-processor link
 *
 * Two independent 8-bit source-synchronous buses, each with its own
 * clock and VALID strobe, plus three single-wire control signals.
 *
 *   Bus A  master -> slave   M.GPIO20..27 -> S.GPIO1..8
 *                            M.GPIO28 (CLK, 33R R1) -> S.GPIO9
 *                            M.GPIO29 (VALID)       -> S.GPIO10
 *
 *   Bus B  slave -> master   S.GPIO11..18 -> M.GPIO30..37
 *                            S.GPIO19 (CLK, 33R R2) -> M.GPIO38
 *                            S.GPIO20 (VALID)       -> M.GPIO39
 *
 * Both buses share the same relative layout, which the PIO programs
 * rely on: CLK == DATA_BASE + 8, VALID == DATA_BASE + 9. That lets one
 * pair of PIO programs serve both directions on both chips with nothing
 * but a different pin base.
 *
 * Control signals (plain SIO, no PIO):
 *   FS      M.GPIO40 -> S.GPIO21   frame-sync / phase strobe (master out)
 *   DB_MS   M.GPIO41 -> S.GPIO22   doorbell, master -> slave
 *   DB_SM   M.GPIO42 <- S.GPIO23   doorbell, slave  -> master
 *
 * NOTE ON GPIO43: the schematic labels M.GPIO43 as "RUNA/SR" (slave
 * reset), but the net only reaches a 10K pull-up to +3V3 (R3) — it is
 * NOT wired to the slave's RUN pin (U6.26), which only sees reset
 * button S4. The firmware therefore cannot reset the slave in hardware;
 * both MCUs must be reset/flashed independently. See README.md.
 * ===================================================================== */

/* ---- Master side (RP2350B / U3) ---- */
#define M_LINK_A_DATA_BASE   20   /* GPIO20..27, master -> slave  */
#define M_LINK_A_CLK         28   /* == DATA_BASE + 8             */
#define M_LINK_A_VALID       29   /* == DATA_BASE + 9             */

#define M_LINK_B_DATA_BASE   30   /* GPIO30..37, slave -> master  */
#define M_LINK_B_CLK         38
#define M_LINK_B_VALID       39

#define M_LINK_FS            40   /* out */
#define M_LINK_DB_OUT        41   /* DB_MS, out */
#define M_LINK_DB_IN         42   /* DB_SM, in  */
#define M_LINK_SLAVE_RUN     43   /* pull-up only — not connected, see above */

/* ---- Slave side (RP2350 / U6) ---- */
#define S_LINK_A_DATA_BASE    1   /* GPIO1..8, master -> slave (RX) */
#define S_LINK_A_CLK          9
#define S_LINK_A_VALID       10

#define S_LINK_B_DATA_BASE   11   /* GPIO11..18, slave -> master (TX) */
#define S_LINK_B_CLK         19
#define S_LINK_B_VALID       20

#define S_LINK_FS            21   /* in  */
#define S_LINK_DB_IN         22   /* DB_MS, in  */
#define S_LINK_DB_OUT        23   /* DB_SM, out */

/* =====================================================================
 * Master peripherals
 * ===================================================================== */

/* HDMI (J5) via HSTX — clock pair first, N before P, matches Murmulator 2 */
#define HDMI_BASE_PIN        12
#define HDMI_PIN_CLKN        12
#define HDMI_PIN_CLKP        13
#define HDMI_PIN_D0N         14
#define HDMI_PIN_D0P         15
#define HDMI_PIN_D1N         16
#define HDMI_PIN_D1P         17
#define HDMI_PIN_D2N         18
#define HDMI_PIN_D2P         19

/* microSD (J7) on SPI0 — SDIO pin names from the schematic in comments */
#define SDCARD_PIN_SPI0_MISO  4   /* SD DAT0    */
#define SDCARD_PIN_SPI0_CS    5   /* SD DAT3/CD */
#define SDCARD_PIN_SPI0_SCK   6   /* SD CLK     */
#define SDCARD_PIN_SPI0_MOSI  7   /* SD CMD     */

/* TDA1387T I2S DAC (U8) */
#define I2S_DATA_PIN          9   /* U8.3 DATA */
#define I2S_CLOCK_PIN_BASE   10   /* U8.1 SCLK = 10, U8.2 LRCK = 11 */

/* WS2812B status LED (LD1) via 330R R11 */
#define M_LED_WS2812_PIN     46

/* 8 MB PSRAM (U2 ESP-PSRAM64H) chip select */
#define M_PSRAM_CS_PIN       47

/* Debug UART header J2: pin1 = GPIO0 (TX), pin2 = GND, pin3 = GPIO1 (RX) */
#define M_UART_ID            uart0
#define M_UART_TX_PIN         0
#define M_UART_RX_PIN         1

/* Spare / unrouted master GPIOs (available for probing) */
#define M_SPARE_GPIO_LIST    { 2, 3, 8, 44, 45 }

/* =====================================================================
 * Slave peripherals
 * ===================================================================== */

/* 8 MB PSRAM (U5 ESP-PSRAM64H) chip select */
#define S_PSRAM_CS_PIN        0

/* Blue status LED (LD2) via 1K R19 — active high */
#define S_LED_PIN            26

/* Debug UART header J4: pin1 = GPIO24 (TX), pin2 = GND, pin3 = GPIO25 (RX) */
#define S_UART_ID            uart1
#define S_UART_TX_PIN        24
#define S_UART_RX_PIN        25

/* Spare / unrouted slave GPIOs */
#define S_SPARE_GPIO_LIST    { 27, 28, 29 }

/* =====================================================================
 * Memory devices (identical part numbers on both sides)
 * ===================================================================== */
#define FRANK_FLASH_PART     "W25Q128JVPIQ"
#define FRANK_FLASH_BYTES    (16u * 1024u * 1024u)
#define FRANK_PSRAM_PART     "ESP-PSRAM64H"
#define FRANK_PSRAM_BYTES    (8u * 1024u * 1024u)

/* XIP windows: CS0 = flash, CS1 = PSRAM (psram_init maps it there).
 *
 * The 0x14000000 aliases bypass the XIP cache entirely. That matters for
 * the PSRAM presence and size probes: through the cached window a write
 * followed by a read of the same address is answered out of the 8 KiB
 * cache, so a missing chip looks present and an address that aliases
 * back onto offset 0 looks like it does not. Throughput measurements
 * deliberately use the cached window, because that is how real code
 * reaches these devices. */
#define FRANK_XIP_FLASH_BASE         0x10000000u
#define FRANK_XIP_PSRAM_BASE         0x11000000u
#define FRANK_XIP_FLASH_NOCACHE_BASE 0x14000000u
#define FRANK_XIP_PSRAM_NOCACHE_BASE 0x15000000u

#endif /* FRANK_CORE2_BOARD_H */

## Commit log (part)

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2025-05-13 MiniFRANK RM1T WIP
2025-05-14 FRANK RM1T updates
2025-05-14 PCB updated
2025-05-18 MiniFRANK RM1P2 WIP
2025-05-19 MiniFRANK RM1P2 1.00
2025-05-23 MiniFRANK RM1P2 1.01
2025-06-01 MiniFRANK RM2 1.02
2025-06-20 MiniFRANK M1 updates
2025-06-20 MiniFRANK RM1P2 released, MiniFRANK M1 in LAB
2025-06-24 NanoFRANK WIP
2025-06-24 Minor updates
2025-07-20 MicroFRANK RM1P2U WIP
2025-07-21 New boards released
    - MiniFRANK M1 added to the hardware dir
    - MicroFRANK RM1P2 added to the hardware dir
    - MicroFRANK RM1P2S archived
2025-07-23 PCB updates
2025-07-23 TF WIP
2025-07-25 TurboFRANK RM1P2 HW 1.00
2025-07-25 MiniFRANK M1 HW 1.01
2025-07-25 MiniFRANK M1 Case added
2025-08-01 MiniFRANK RM1P2H
2025-08-01 MiniFRANK RM1P2H HW 1.0
2025-08-04 TinyFRANK RM1P1 HW 1.00
2025-08-10 TurboFRANK WIP
2025-08-11 TurboFRANK RM1P2 HW 1.01
2025-08-11 TurboFRANK Cleanup
2025-08-11 Minor updates to TurboFRANK RM1P2
2025-08-11 FRANK RM1P2 Added
2025-08-11 FRANK RM1P2 HW 1.00
2025-08-20 FRANK One HW 1.00
2025-08-20 FRANK M2 HW 1.04
2025-08-20 Archived microfrank_rm1p2su
2025-08-20 FRANK Exp WIP
2025-08-21 FRANK Exp HW 1.00
2025-09-02 FRANK RM1P2 HW 1.01
2025-09-02 Minor updated to TinyFRANK 1.00
2025-09-02 MiniFRANK RM1P2H HW 1.01
2025-09-02 Cleanup
2025-09-02 Moved tested PCBs from LAB
2025-09-05 FRANK M1 WIP
2025-09-06 FRANK M2 Case
2025-09-06 Cleanup & Minor Updates
2025-09-08 Fastbeta WIP
2025-09-08 Minor changes
2025-09-10 Fastbeta PWT WIP
2025-09-10 FRANK Fastbeta WIP
2025-09-10 Fastbeta Modern WIP
2025-09-10 Fastbeta Modern HW 1.00
2025-09-14 Boards WIP
2025-09-14 FRANK Fastbeta PWT, One WIP
2025-09-17 FRANK One HW 1.01
2025-09-17 TinyFRANK RM1P2 WIP
2025-09-17 TinyFRANK WIP
2025-09-18 TinyFRANK RM1P2 1.00
2025-09-18 Gerbers added
2025-09-23 Fastbeta PWT 1.02
2025-09-26 New boards + Bugfixes
2025-09-26 FRANK board updates
2025-10-04 FRANK RM2 WIP
2025-10-06 Board updates
2025-10-06 FRANK One RM2P2 HW 1.00
2025-10-07 EXT SOUND TS 1.00
2025-10-09 FRANK M1 HW 2.02
2025-10-10 FRANK One RM2 HW 1.01
2025-10-10 FRANK RM2 HW 1.01
2025-10-29 FRANK M1 2.03 WIP
2025-10-31 USB2PS2 HW 3.00
2025-11-03 FRANK One RM2 HW 1.03
2025-11-16 FRANK Fastbeta PWT 1.04 Release + Case
2025-11-20 Minor changes to FPWT & Case for FPWT 1.04
2025-11-24 FRANK M1 2.03 & xt8086 WIP
2025-11-24 xt8086 WIP
2025-11-24 xt8086 cleanup
2025-11-24 xt8086 HW 1.00
2025-11-25 Missing diode added to xt8086 project
2025-12-03 Marked HW 2.03 as unstable
2025-12-17 FRANK M1 2.04
2025-12-23 TinyFRANK RM2 WIP
2026-01-02 FRANK M1 + TinyFRANK RM2 WIP
2026-01-02 HW 2.05 WIP
2026-01-05 Frank boards WIP
2026-01-05 TinyFRANK RM1 HW 1.00
2026-01-05 FRANK M2 HW 2.05
2026-01-27 New HW releases, repository cleanup
2026-01-27 Assembly file renamed
2026-02-01 MiniFRANK RM2 WIP
2026-02-02 MiniFRANK WIP
2026-02-03 MiniFRANK RM2 rounded tracks
2026-02-04 MiniFRANK RM2 HW 1.00
2026-03-10 LAB WIP
2026-03-11 FRANK M2 Pro WIP
2026-03-11 FRANK M1 Pro HW 1.00
2026-03-15 MiniFRANK RM2 Pro WIP
2026-03-17 MiniFRANK RM2 Pro HW 1.00
2026-03-23 MiniFRANK RM2P2 WIP
2026-03-23 Hecate updated
2026-03-24 Bugfixes
2026-03-27 MiniFRANK M2P2 HW 1.04
2026-04-15 Repo cleanup and restructuring
    - Renamed tools/ to accessories/
    - Lowercased directory names (LIBS→libs, 3D→3d, DOCS→docs, GERBERS→gerbers, CASE→case)
    - Updated all KiCad references (fp-lib-table, sym-lib-table, kicad_pro, footprints, PCBs)
    - Removed unused footprints, symbols, 3D models, and legacy files (.lib/.dcm/.mod)
    - Removed temp files (.DS_Store, .bak, .lck, fp-info-cache, .kicad_prl, .round-tracks-config)
    - Cleaned stale sym-lib-table entries
2026-04-15 Clean up lab/frank_pro_m2 and lab/xt8086
    - Removed unused footprints, symbols, 3D models, legacy files
    - Renamed directories to lowercase (LIBS, 3D, DOCS, GERBERS, CASE)
    - Updated KiCad references, cleaned stale sym-lib-table entries
    - Removed temp files (.bak, fp-info-cache, .kicad_prl, .round-tracks-config)
2026-04-16 KiCad 10 Update
2026-04-17 TinyFRANK M2P2 WIP
2026-04-20 Clean up lab/xt8086 and lab/tinyfrank_m2p2
    - Removed unused 3D models (26 from xt8086, 7 from tinyfrank_m2p2)
    - Removed temp files from tinyfrank_m2p2
    - Updated 3D path references to lowercase
    - Added .history/ to .gitignore
2026-04-20 Rename footprints, 3D models to KiCad standard naming
    lab/xt8086:
    - Renamed 22 footprints (spaces/parens/IPNs -> KiCad style)
    - Renamed 13 3D models, normalized all to .step
    - Fixed FRANK: prefix -> xt8086: in symbol/schematic refs
    - Fixed bare 3D model path without ${KIPRJMOD} prefix
    lab/frank_pro_m2:
2026-04-20 Rename footprints and 3D models in lab/tinyfrank_m2p2
    - Removed 2 unused footprints (ESP-01, SO-16)
    - Renamed 18 footprints to KiCad standard naming
    - Renamed 15 3D models, normalized all to .step
    - Fixed wrong library prefixes (FRANK:, LIBS:, MSK12C02:, etc.)
2026-04-20 Rename and localize hardware/frank_m2 footprints, 3D models
    - Removed 5 unused footprints, 1 unused 3D model
    - Renamed 28 footprints to KiCad standard naming
    - Renamed 30 3D models, normalized all to .step
    - Copied 12 system 3D models (KiCad built-in) to local 3d/ dir
    - Replaced all ${KICADx_3DMODEL_DIR} refs with ${KIPRJMOD}/3d/
    - Fixed wrong library prefixes (LIBS:, DC-005-5A-2.0:, etc.)
2026-04-20 Make hardware/frank_m2 fully self-contained
    - Extracted 16 symbols from KiCad global libraries into FRANK.kicad_sym
    (LM358, NCP1117, Conn_01x03_Pin, USB_A_Stacked, SW_Push, etc.)
    - Merged 3 standalone symbol files into FRANK.kicad_sym, removed originals
    - Updated all lib_id references from global (Device:, Connector:, etc.) to FRANK:
    - Cleaned sym-lib-table to single FRANK entry
    - Project now has zero external library dependencies
2026-04-20 Add missing parent symbols for LM358 and NCP1117
    LM358 extends LM2904, NCP1117-3.3_SOT223 extends AP1117-15.
    Without the parents, KiCad can't render these symbols.
2026-04-22 Move lab/ to frank-lab repo, restore minifrank_m2p2 v1.04 from master
2026-04-22 Move hardware/frank_m2 to frank-lab repo, restore v2.06 from master
2026-04-22 Move hardware/frank_m1 to archive
2026-04-22 Update README: remove archived boards, link to frank-lab
2026-04-22 Remove leftover frank_m2 files not present in v2.06
2026-05-07 New boards added
2026-05-07 Board archived + new boards from lab
2026-05-07 Docs added
2026-05-07 Add board renders and silkscreen wireframes to docs
    Two scripts driven by kicad-cli generate visual assets for the
    README and per-board guides:
    - scripts/render-board-svgs.sh produces 2D silkscreen + F.Fab/B.Fab
    SVGs (top + bottom per board) used to illustrate component
    placement in the soldering sections.
    - scripts/render-board-3d.sh produces 3D ray-traced isometric PNGs
2026-05-07 MiniFRANK: localize libs, recolor connectors, split audio jacks
    - Split J7 (TapeIn) and J11 (AudioOut) into per-instance footprints
    and 3D models with light red and green plastic
    - Unify connector metal shells to neutral 0.65 gray (USB, USB-C, SD,
    PS/2, switches, DB9, VGA, HDMI)
    - Color VGA plastic body blue
    - Replace HDMI IGES with project-local STEP and align footprint
2026-05-07 Propagate connector colors and audio jack split to all boards
    - Replace USB, USB-C, SD, PS/2, slide switch, tact switch, DB9, VGA,
    and HDMI 3D models in frank, frank_pga, and microfrank with the
    recolored MiniFRANK versions (0.65 gray metal, blue VGA plastic)
    - Reset HDMI footprint offset/rotation to identity since the new
    HDMI_Female.step is the KiCad HDMI_A geometry
    - Split audio jack into TapeIn (red) and AudioOut (green) variants
2026-05-07 FRANK PGA: opaque solder mask to remove ENIG gold bleed-through
    The translucent black mask let the ENIG copper finish tint the rendered
    surface brown. Switch FRANK PGA to a fully opaque mask alpha so the
    board renders neutral black.
2026-05-07 Render: neutralize FRANK PGA brown tint without losing trace visibility
    - Add per-board copper finish selector; use Immersion silver for
    FRANK PGA so trace bleed-through stops tinting the surface gold
    - Shift FRANK PGA mask color to a slightly cool dark gray to cancel
    the residual copper warmth and land on neutral near-black
    - Regenerate iso renders for all four boards
2026-05-07 Render: per-board iso rotation; align MicroFRANK with the other boards
    MicroFRANK's canvas orientation differs from the other boards, so
    the default isometric rotation produced a mirrored framing. Add an
    iso_rotate() override and rotate MicroFRANK -120° around Z so its
    HDMI/USB layout matches frank, frank_pga, and minifrank.
2026-05-07 docs: promote FRANK PGA as the flagship, FRANK as socketed alternative
    Reorder boards table and comparison columns in README so FRANK PGA leads,
    update both per-board guide intros to match, and normalize BOM "Reference
    style" headers to "Ref". Includes refreshed 3D renders for FRANK, FRANK PGA
    and MiniFRANK.
2026-05-07 docs: fix flashing instructions, list firmware repos, document Hecate
    - frank_pga.md: correct first-boot to describe UF2 flashing via RP BOOT +
    RP Reset; remove false "easier than FRANK" claim about on-board buttons
    since both boards have BOOTSEL access.
    - frank.md: rename Nyx 2 to Nyx.
    - README.md: replace single rh1tech search link with an explicit list of
    all firmware repos; describe what ships in software/ (Hecate UF2 for
2026-05-08 docs: add Russian translations of board guides
    Adds frank.ru.md, frank_pga.ru.md, minifrank.ru.md, microfrank.ru.md.
    Translations are formal-register and avoid English calques. Image paths
    match the English originals so the site's update script handles them
    the same way.
    Also includes the in-progress 3D render updates and the matching
    render-board-3d.sh changes that were pending in the working tree.
2026-05-09 fix: correct PSRAM part to ESP-PSRAM64H and clean up doc inaccuracies
    Hardware:
    - Rename ESP-PSRAM32 to ESP-PSRAM64H across MicroFRANK and MiniFRANK
    symbol libraries, schematics, PCB value fields and the SO-8 footprint
    default. Update datasheet URL to Espressif's combined ESP-PSRAM64 /
    ESP-PSRAM64H sheet.
    Docs:
2026-05-10 docs: refine board docs and Russian translations
    EN: tighten phrasing, replace inaccurate audio path description
    (CD4069UBM is for tape input, not a PWM filter), drop primary/
    secondary video labels (output is firmware-selected), name the
    ESP-01S firmware (frank-netcard), and standardize jack/voltage
    formatting.
    RU: align with the same content corrections; replace literal
2026-05-11 ci: add notify-consumers workflow
2026-05-30 Nyx HW 2.02 Added
2026-06-02 xt8086 board added
2026-06-04 docs: standardize naming (assembly.pdf, bom.html, schematics.pdf)
    Latest versions:
    - frank: 2.09
    - frank_pga: 1.03
    - microfrank: 1.02
    - minifrank: 1.07
    - nyx: 2.03
2026-06-28 MiniFRANK: new board version
2026-06-28 feat: add megafrank, zerofrank boards and turbosound, hecate modules
    Promoted from frank-lab into hardware/. Adds KiCad projects, gerbers and
    fabrication docs, 3D renders and silkscreen SVGs, and EN/RU assembly guides.
    README updated: boards table, comparison table, new Modules section, repo
    layout and documentation links.
    - megafrank: maximal PGA2350 board with on-board TurboSound, RTC, dual power
    - zerofrank: minimal RP2350A board, HDMI only, no PSRAM
